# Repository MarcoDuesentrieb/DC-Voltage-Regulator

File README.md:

# DC-Voltage-Regulator
DC Voltage Regulator PCB for Lecture [MScTI_MES] Microcontroller Based Embedded Systems

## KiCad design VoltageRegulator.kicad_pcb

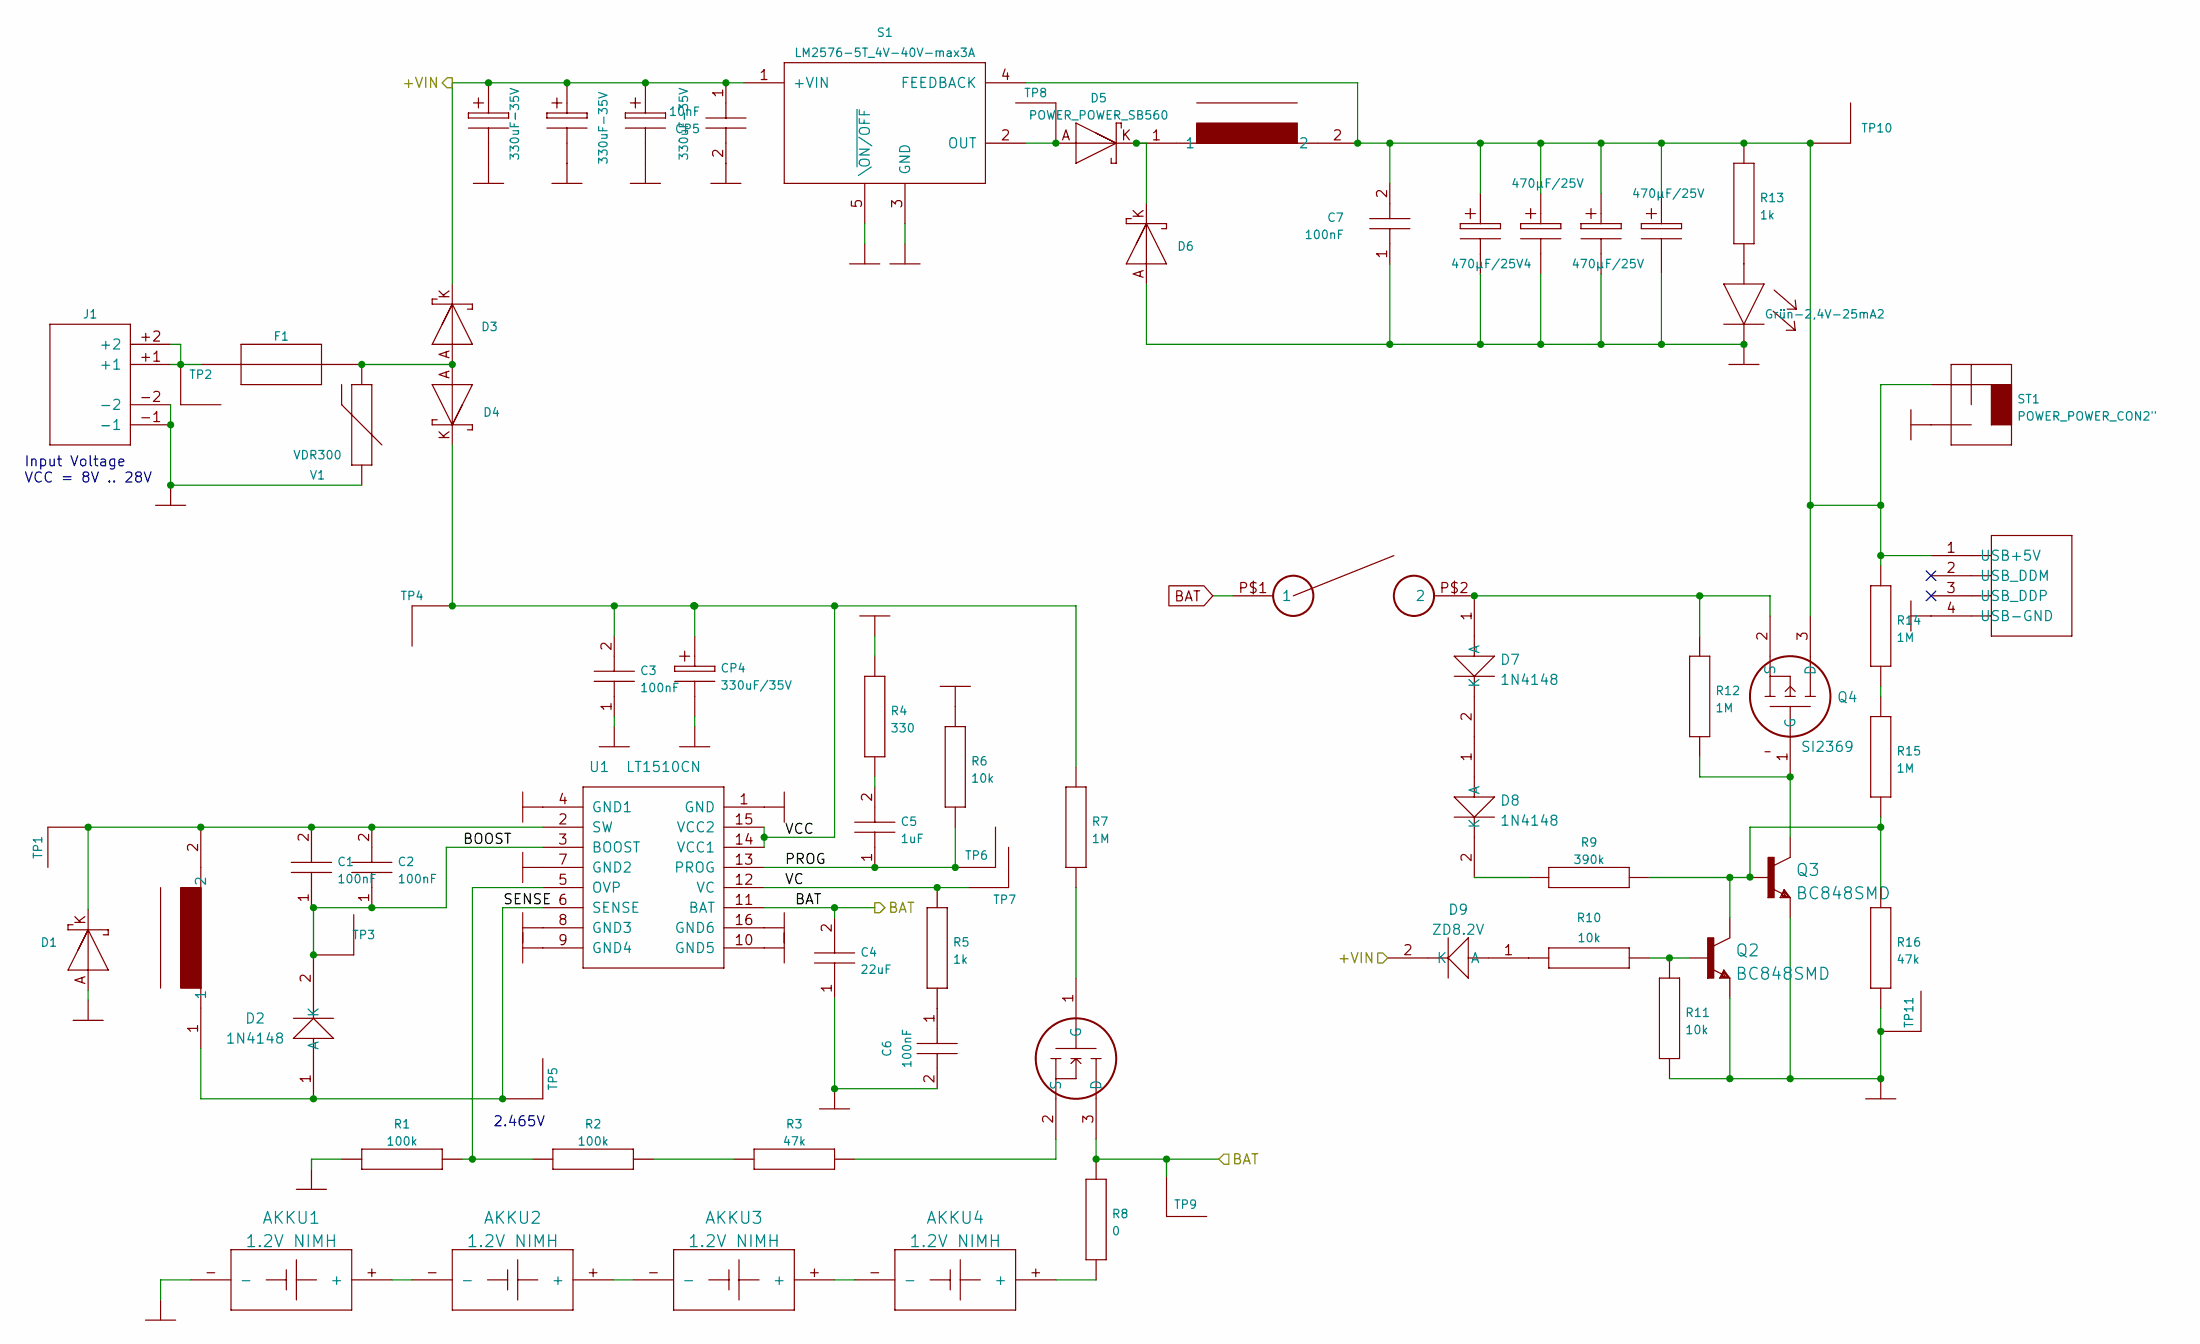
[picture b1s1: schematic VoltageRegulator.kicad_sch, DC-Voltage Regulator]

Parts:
AKKU1, AKKU2, AKKU3, AKKU4: 1.2V NIMH; POWER_POWER_AKKU_AA
C1, C2, C3, C6, C7: 100nF; C1206
C4: 22uF; C1206
C5: 1uF; C1206
CP1, CP2, CP3: 330uF-35V; POWER_POWER_C-POL
CP4: 330uF/35V; POWER_POWER_C-POL
CP5: 10nF; C1206
CP6: 470μF/25V4; POWER_POWER_C-POL
CP7, CP8, CP9: 470μF/25V; POWER_POWER_C-POL
D1, D3, D4, D6: POWER_POWER_SB560"; POWER_POWER_DO201AD
D2, D7, D8: 1N4148; C1206
D5: POWER_POWER_SB560; POWER_POWER_DO201AD
D9: ZD8.2V; C1206
F1: POWER_POWER_FUSE"; POWER_POWER_DIP2-300R
J1: POWER_POWER_ROKA-PWR-IN
L1, L2: POWER_POWER_SPULE_STEHEND
LED1: Grün-2,4V-25mA2; POWER_POWER_LED-3MM
Q1: FDN337N; SOT23
Q2, Q3: BC848SMD; SOT23
Q4: SI2369; SOT23
R1, R2: 100k; R0805
R3, R16: 47k; R0805
R4: 330; R0805
R5, R13: 1k; R0805
R6, R10, R11: 10k; R0805
R7, R12, R14, R15: 1M; R0805
R8: 0; R0805
R9: 390k; R0805
S1: LM2576-5T_4V-40V-max3A; POWER_POWER_TO-220_5_short
ST1: POWER_POWER_CON2"; POWER_POWER_CON2
ST2: POWER_POWER_USBA
TP1, TP2, TP3, TP4, TP5, TP6, TP7, TP8, TP9, TP10, TP11: POWER_POWER_TSTPIN"; POWER_POWER_TSTPIN
U1: LT1510CN; SO16
U2: POWER_POWER_SWITCH_ON
V1: VDR300; POWER_POWER_VDR

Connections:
/+VIN: CP1.+, CP2.+, CP3.+, CP5.1, D3.K, D9.2 (K), S1.1 (+VIN)
/BOOST: C1.1, C2.1, D2.2 (K), TP3.P$1, U1.3 (BOOST)
/PROG: C5.1, R6.1, TP6.P$1, U1.13 (PROG)
/SENSE: D2.1 (A), L1.1, TP5.P$1, U1.6 (SENSE)
/VC: R5.2, TP7.P$1, U1.12 (VC)
/VCC: C3.2, CP4.+, D4.K, R7.2, TP4.P$1, U1.14 (VCC1), U1.15 (VCC2)
BAT: C4.2, Q1.3 (D), R8.2, TP9.P$1, U1.11 (BAT), U2.P$1 (1)
GND: AKKU1.-, AKKU1.P1, AKKU2.P1, AKKU3.P1, AKKU4.P1, C3.1, C4.1, C6.2, C7.1, CP1.-, CP2.-, CP3.-, CP4.-, CP5.2, CP6.-, CP7.-, CP8.-, CP9.-, D1.A, D6.A, J1.-1, J1.-2, LED1.K, Q2.2 (E), Q3.2 (E), R1.1, R4.2, R6.2, R11.1, R16.1, S1.3 (GND), S1.5 (\~ON/OFF), ST1.GND, ST2.4 (USB-GND), TP11.P$1, U1.1 (GND), U1.4 (GND1), U1.7 (GND2), U1.8 (GND3), U1.9 (GND4), U1.10 (GND5), U1.16 (GND6), V1.P$1
unnamed: AKKU1.+, AKKU2.-
unnamed: AKKU2.+, AKKU3.-
unnamed: AKKU3.+, AKKU4.-
unnamed: AKKU4.+, R8.1
unnamed: C1.2, C2.2, D1.K, L1.2, TP1.P$1, U1.2 (SW)
unnamed: C5.2, R4.1
unnamed: C6.1, R5.1
unnamed: C7.2, CP6.+, CP7.+, CP8.+, CP9.+, L2.2, Q4.3 (D), R13.2, R14.2, S1.4 (FEEDBACK), ST1.+5V, ST2.1 (USB+5V), TP10.P$1
unnamed: D3.A, D4.A, F1.P$2, V1.P$2
unnamed: D5.A, S1.2 (OUT), TP8.P$1
unnamed: D5.K, D6.K, L2.1
unnamed: D7.1 (A), Q4.2 (S), R12.2, U2.P$2 (2)
unnamed: D7.2 (K), D8.1 (A)
unnamed: D8.2 (K), R9.1
unnamed: D9.1 (A), R10.2
unnamed: F1.P$1, J1.+1, J1.+2, TP2.P$1
unnamed: LED1.A, R13.1
unnamed: Q1.1 (G), R7.1
unnamed: Q1.2 (S), R3.2
unnamed: Q2.1 (B), R10.1, R11.2
unnamed: Q2.3 (C), Q3.1 (B), R9.2
unnamed: Q3.3 (C), Q4.1 (G), R12.1
unnamed: R1.2, R2.1, U1.5 (OVP)
unnamed: R2.2, R3.1
unnamed: R14.1, R15.2
unnamed: R15.1, R16.2

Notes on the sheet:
2.465V
Input Voltage VCC = 8V .. 28V

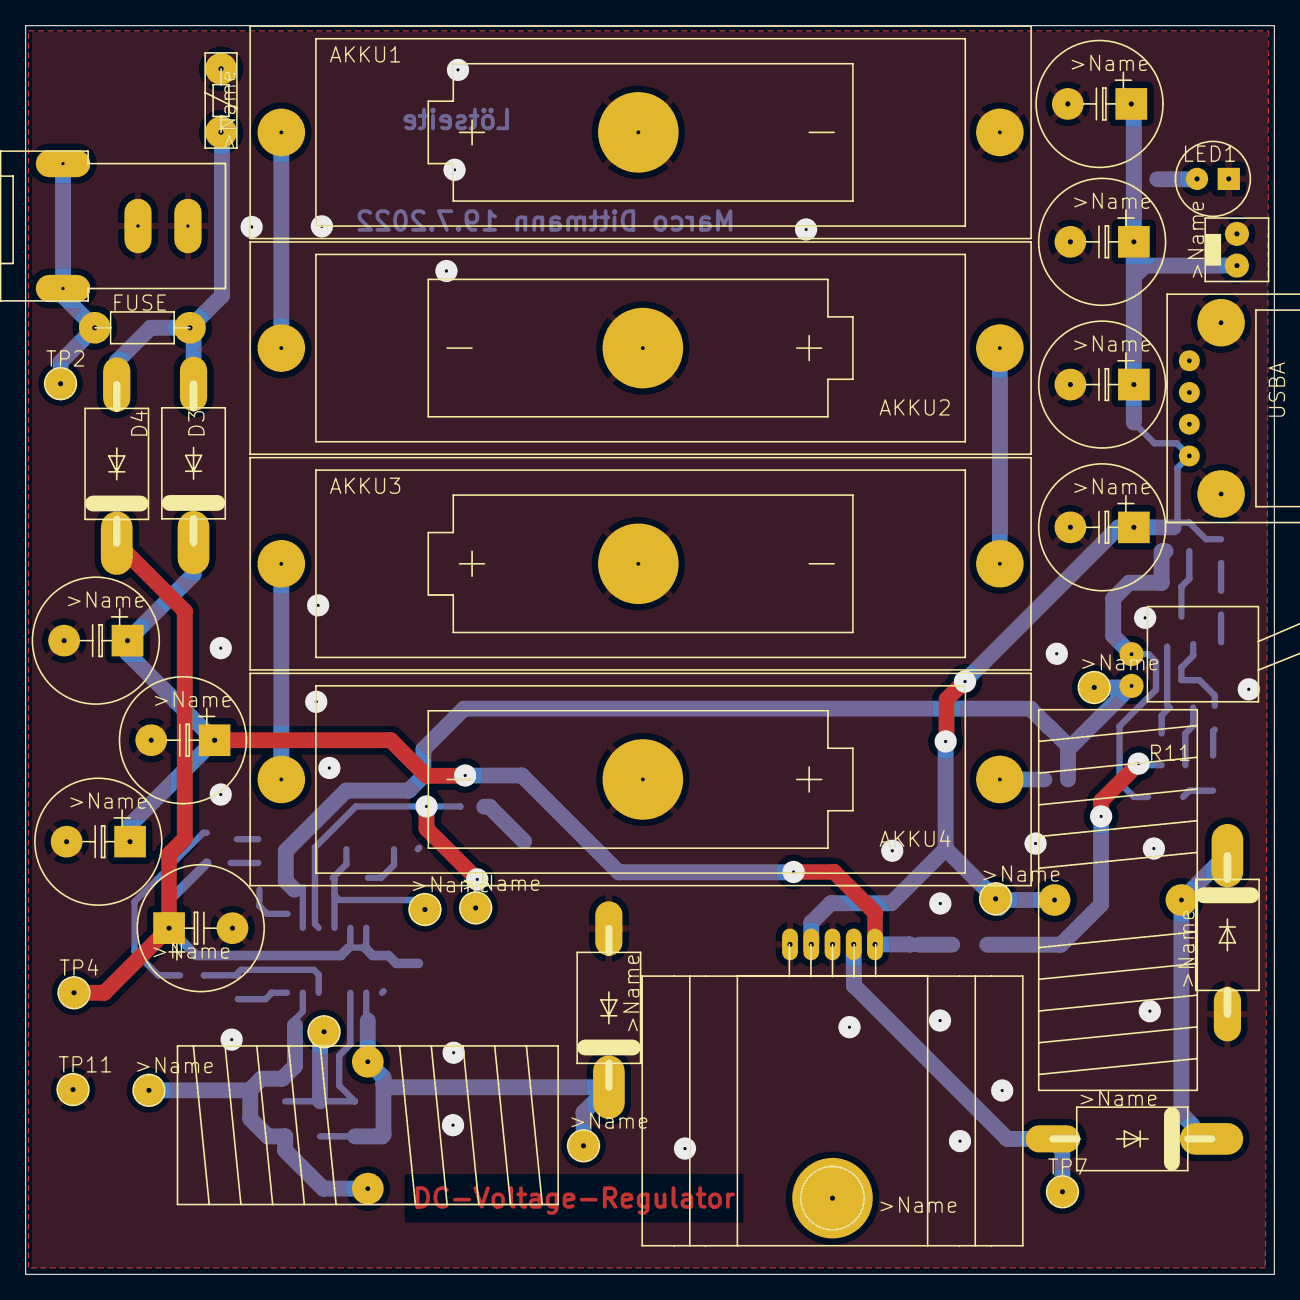
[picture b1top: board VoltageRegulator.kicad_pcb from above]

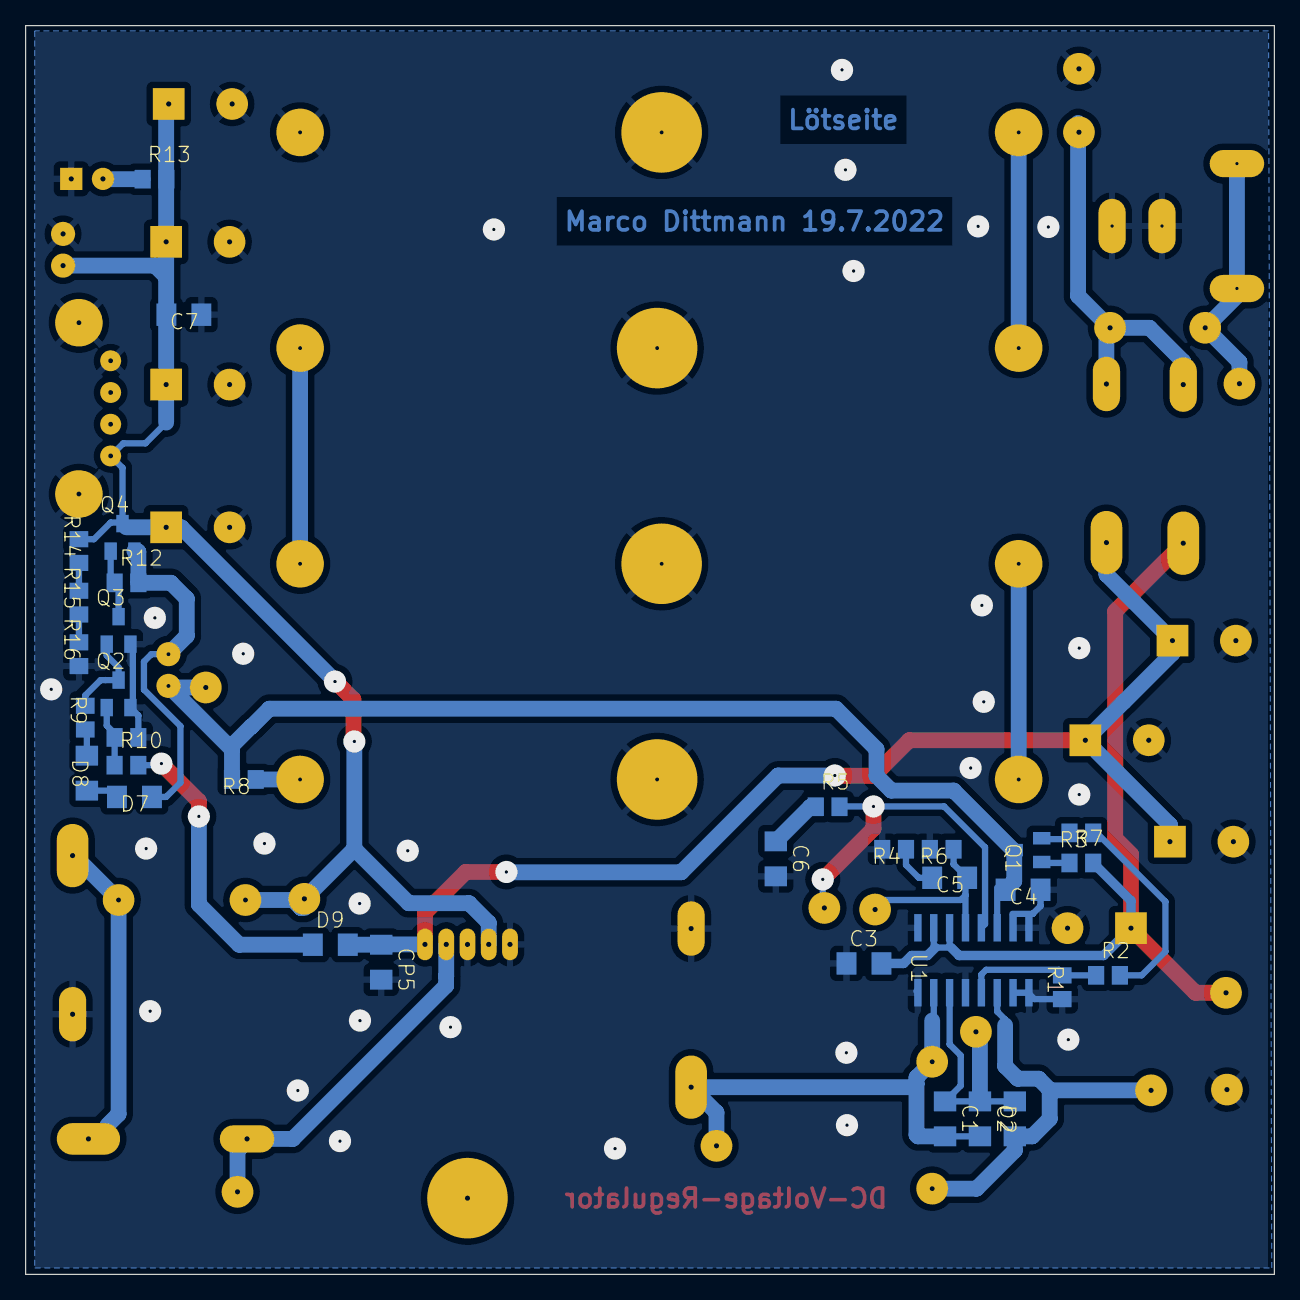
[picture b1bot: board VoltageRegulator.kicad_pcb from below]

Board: 2 copper layers, 100.0 x 100.0 mm, 71 parts (33 on the bottom side), 34 nets.

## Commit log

2022-07-18 Layout almost finished
2022-08-15 Version 1.0
